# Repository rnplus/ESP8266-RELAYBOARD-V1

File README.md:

# ESP8266 relay board: hardware
In this repository you can find the eagle design files for our ESP8266 relay board.

Firmware for this board can be found here:
https://github.com/rnplus/ESP8266-relay-board-firmware

License: CC BY-SA 3.0

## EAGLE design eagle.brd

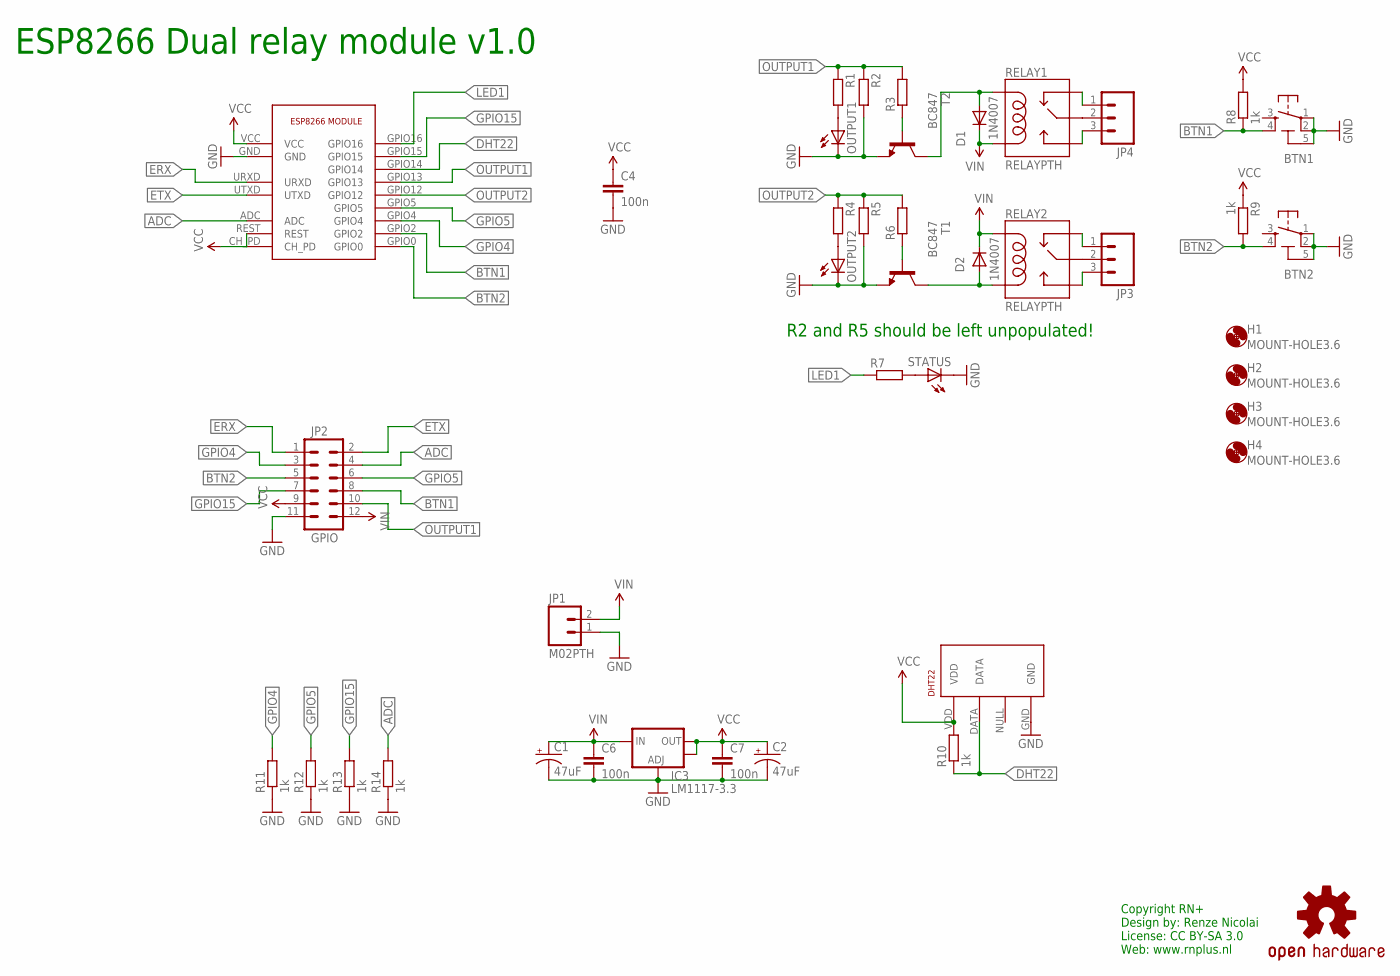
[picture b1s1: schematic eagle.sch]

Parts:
BTN1, BTN2: SMARTPRJ_TS42
C1, C2: 47uF; PANASONIC_D
C4, C6, C7: 100n; C0805K
D1, D2: 1N4942; DO41-10
DHT22: RHT03_DHT-22_AM2302; RHT03_DHT-22
ESP8266: ESP8266ESP-07; ESP-12
H1, H2, H3, H4: MOUNT-HOLE3.6; 3,6
IC3: LM1117-3.3; SOT223
JP1: M02PTH; 1X02
JP2: GPIO; 2X6
JP3, JP4: M03-SCREW-5MM; SCREWTERMINAL-5MM-3
LOGO1: OSHW-LOGOL; OSHW-LOGO-L
OUTPUT1, OUTPUT2: LEDCHIP-LED0805; CHIP-LED0805
R1, R2, R3, R4, R5, R6, R7: SMARTPRJ_R-EU_M0805; SMARTPRJ_M0805
R8, R9, R10, R11, R12, R13, R14: 1k; SMARTPRJ_M0805
RELAY1, RELAY2: RELAYPTH; SRD-05VDC-SL-C
STATUS: LEDCHIP-LED0805; CHIP-LED0805
T1, T2: BC847; SOT23

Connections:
ADC: ESP8266.ADC, JP2.4, R14.2
BTN1: BTN1.4, ESP8266.GPIO2, JP2.8, R8.1
BTN2: BTN2.4, ESP8266.GPIO0, JP2.5, R9.2
DHT22: DHT22.DATA, ESP8266.GPIO14, R10.1
ERX: ESP8266.URXD, JP2.1
ETX: ESP8266.UTXD, JP2.2
GND: BTN1.1, BTN1.2, BTN1.5 (5-GND), BTN2.1, BTN2.2, BTN2.5 (5-GND), C1.-, C2.-, C4.2, C6.2, C7.2, DHT22.GND, ESP8266.GND, IC3.1 (ADJ), JP1.1, JP2.11, OUTPUT1.C, OUTPUT2.C, R2.2, R5.2, R11.1, R12.1, R13.1, R14.1, STATUS.C, T1.2 (E), T2.2 (E)
GPIO4: ESP8266.GPIO4, JP2.3, R11.2
GPIO5: ESP8266.GPIO5, JP2.6, R12.2
GPIO15: ESP8266.GPIO15, JP2.7, R13.2
LED1: ESP8266.GPIO16, R7.1
unnamed: D2.A, RELAY2.COIL0, T1.3 (C)
unnamed: D1.A, RELAY1.COIL1, T2.3 (C)
unnamed: JP3.2, RELAY2.SWCOMMON
unnamed: JP4.2, RELAY1.SWCOMMON
unnamed: JP4.1, RELAY1.SWCLOSED (SWCLOSE)
unnamed: JP4.3, RELAY1.SWOPEN
unnamed: JP3.3, RELAY2.SWOPEN
unnamed: JP3.1, RELAY2.SWCLOSED (SWCLOSE)
unnamed: R3.1, T2.1 (B)
unnamed: R6.1, T1.1 (B)
unnamed: OUTPUT2.A, R4.2
unnamed: R7.2, STATUS.A
unnamed: OUTPUT1.A, R1.2
OUTPUT1: ESP8266.GPIO13, JP2.10, R1.1, R2.1, R3.2
OUTPUT2: ESP8266.GPIO12, R4.1, R5.1, R6.2
VCC: C2.+, C4.1, C7.1, DHT22.VDD, ESP8266.CH_PD, ESP8266.REST, ESP8266.VCC, IC3.2 (OUT), IC3.4 (OUT), JP2.9, R8.2, R9.1, R10.2
VIN: C1.+, C6.1, D1.C, D2.C, IC3.3 (IN), JP1.2, JP2.12, RELAY1.COIL0, RELAY2.COIL1

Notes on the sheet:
Copyright RN+ Design by: Renze Nicolai License: CC BY-SA 3.0 Web: www.rnplus.nl
ESP8266 Dual relay module v1.0
1N4007
R2 and R5 should be left unpopulated!

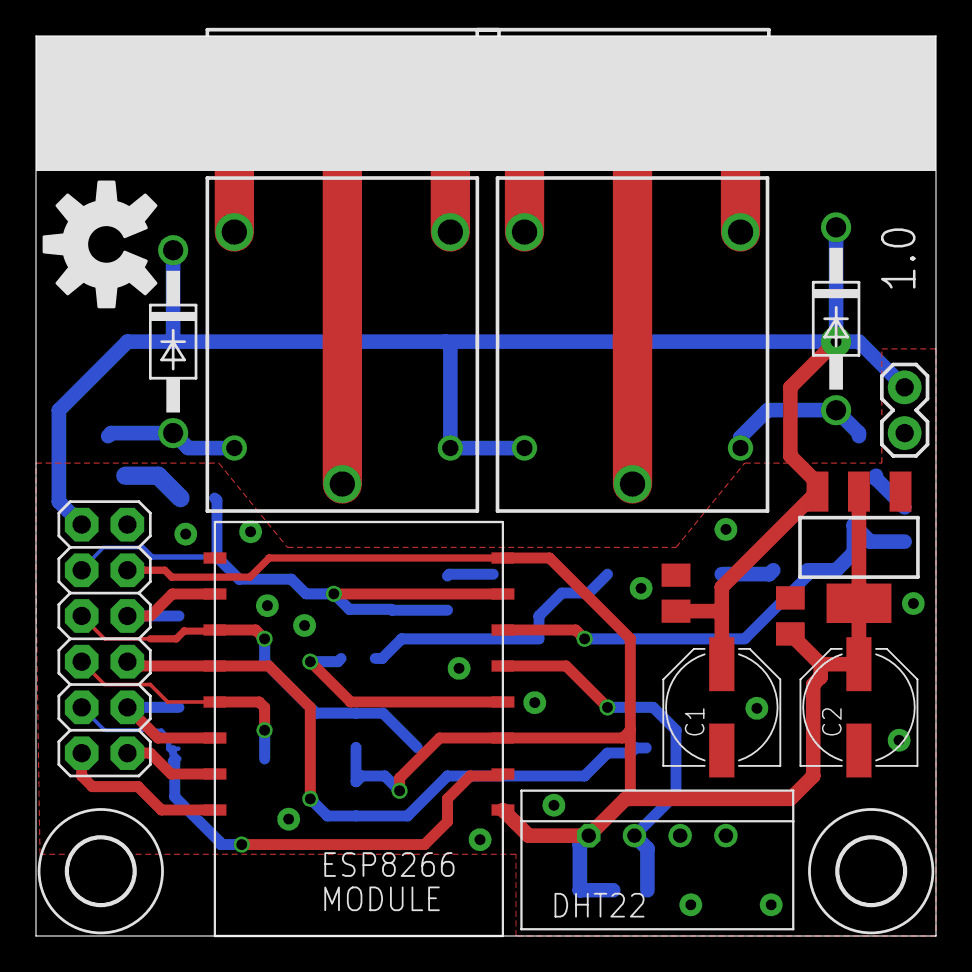
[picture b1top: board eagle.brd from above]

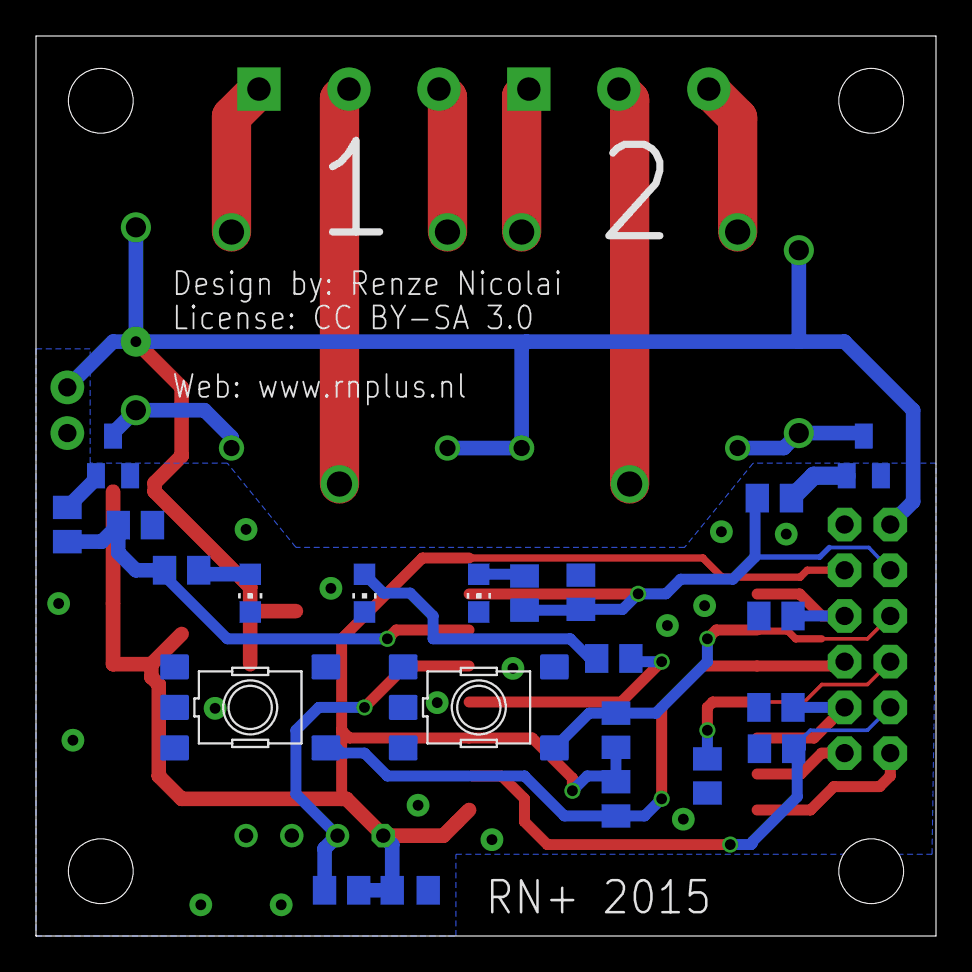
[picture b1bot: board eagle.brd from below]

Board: 2 copper layers, 50.0 x 50.0 mm, 42 parts (22 on the bottom side), 28 nets.

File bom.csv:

Name;Value;Device;Package;QTY;MPN;Manufacturer;Comment
OUTPUT1, OUTPUT2, STATUS;;LEDCHIP-LED0805;CHIP-LED0805;3;SML-LXT0805GW-TR;Lumex;
JP3, JP4;;M03-SCREW-5MM;SCREWTERMINAL-5MM-3;2;1935174;Phoenix Contact;
DHT22;;RHT03_DHT-22_AM2302;RHT03_DHT-22;1;385;Adafruit; Adafruit Accessories DHT22 Temp/Humidity Sensor
R3, R6;2k;SMARTPRJ_R-EU_M0805;SMARTPRJ_M0805;2;CRCW08052K00FKEA;Vishay;
R1, R4, R7;300ohm;SMARTPRJ_R-EU_M0805;SMARTPRJ_M0805;3;CRCW0805300RJNEA;Vishay Dale;
C4, C6, C7;100n;C-EUC0805K;C0805K;3;08055C104KAT2A;AVX;
D1, D2;1N4942;1N4942;DO41-10;2;1N4942GP-E3/54;Vishay Semiconductor;
R8, R9, R10, R11, R12, R13, R14;1k;SMARTPRJ_R-EU_M0805;SMARTPRJ_M0805;7;CRCW08051K00FKEA;Vishay;
C1, C2;47uF;CAP_POLD;PANASONIC_D;2;EEE-1CA470SP;Panasonic;
T1, T2;BC847;BC847;SOT23;2;BC847ALT1G;ON Semiconductor;
ESP8266;ESP8266ESP-07;ESP8266ESP-07;ESP-12;1;2491;Adafruit;
JP2;GPIO;M06X2PTH_FEMALE;2X6;1;67997-112HLF;FCI;
IC3;LM1117-3.3;V_REG_LM1117SOT223;SOT223;1;LM1117MPX-3.3/NOPB;Texas Instruments;
JP1;M02PTH;M02PTH;1X02;1;640456-2;TE Connectivity;
RELAY1, RELAY2;RELAYPTH;RELAYPTH;SRD-05VDC-SL-C;2;G5LE-1-DC5;;
BTN1, BTN2;SMARTPRJ_TS42;SMARTPRJ_TS42;SMARTPRJ_TS42;2;1-1437565-8;TE Connectivity / AMP ;
H1, H2, H3, H4;MOUNT-HOLE3.6;MOUNT-HOLE3.6;3,6;;DUMMY;DUMMY;
LOGO1;OSHW-LOGOL;OSHW-LOGOL;OSHW-LOGO-L;;DUMMY;DUMMY;
R2, R5;Dummy;SMARTPRJ_R-EU_M0805;SMARTPRJ_M0805;;DUMMY;DUMMY;

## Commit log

2015-04-16 Initial version
2015-04-16 Added readme
2015-04-16 Added link to firmware
2016-02-22 Add project image
2016-03-04 Increased drill size for relays
2016-03-04 Increased drill size for relays to 1.4mm
2016-03-04 Add BOM
2016-03-04 use commas as seperator
2016-03-04 Added extra bom with links to chinese sellers, added extra photo
2016-03-04 Added extra bom and extra photo
2016-03-04 Exta photo

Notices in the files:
parts and their libraries:
SparkFun-PowerIC: Licensing: Creative Commons ShareAlike 4.0 International - https://creativecommons.org/licenses/by-sa/4.0
